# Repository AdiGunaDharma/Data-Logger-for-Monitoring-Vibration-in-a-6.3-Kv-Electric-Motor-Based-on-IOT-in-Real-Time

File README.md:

# Data-Logger-for-Monitoring-Vibration-in-a-6.3-Kv-Electric-Motor-Based-on-IOT-in-Real-Time
**Eagle Electronic Layout**
  1. Top Layout

  2. Bottom Layout

**Main**
  1. Vibration Measurement Points and Vibration Measurement Templates at Jeranjang PLTU

  2. Measurement Diagrams on Prototypes

  3. Arduino IDE Software Display and Blynk Application

  4. Sensor Data Amplifier Circuit

  5. Prototype Work System Flowchart

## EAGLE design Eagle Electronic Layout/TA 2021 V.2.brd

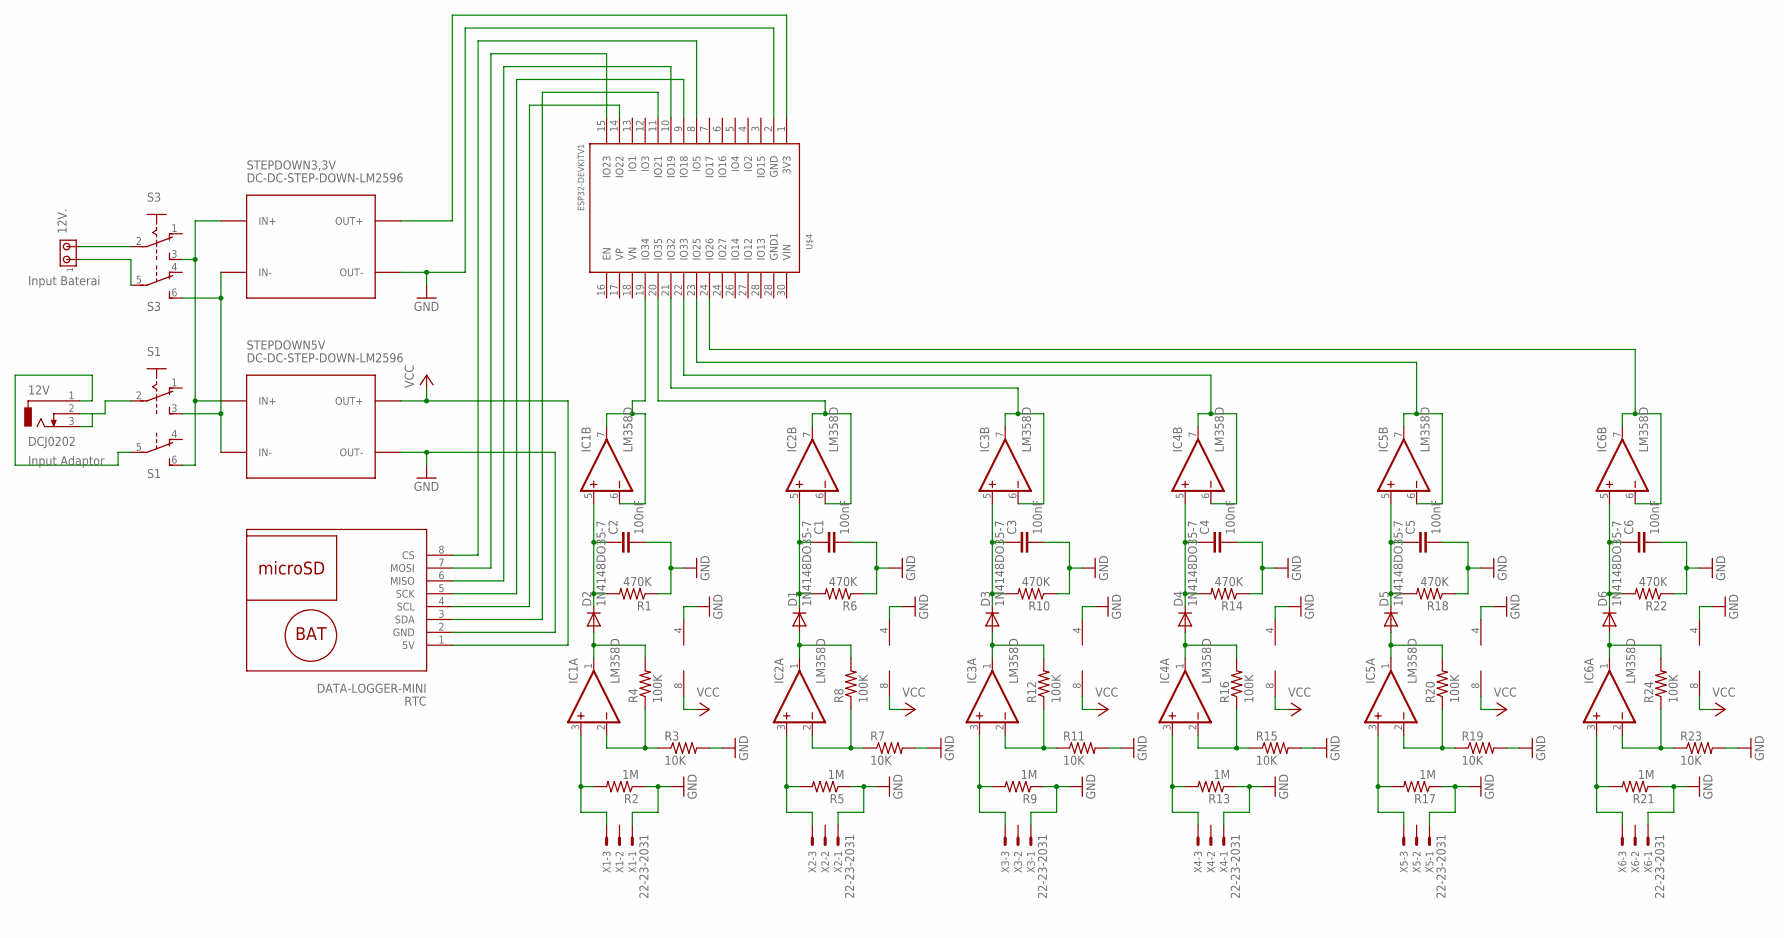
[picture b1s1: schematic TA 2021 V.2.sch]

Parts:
12V: DCJ0202
12V.: MTA02-156; 1X2MTA
C1, C2, C3, C4, C5, C6: 100nF; C075-032X103
D1, D2, D3, D4, D5, D6: 1N4148DO35-7; DO35-7
IC1, IC2, IC3, IC4, IC5, IC6: LM358D; SO08
R1, R6, R10, R14, R18, R22: 470K; 0207/10
R2, R5, R9, R13, R17, R21: 1M; 0207/10
R3, R7, R11, R15, R19, R23: 10K; 0207/10
R4, R8, R12, R16, R20, R24: 100K; 0207/10
RTC: DATA-LOGGER-MINI
S1, S3: A68-A31
STEPDOWN3,3V, STEPDOWN5V: DC-DC-STEP-DOWN-LM2596
U$4: ESP32DEVKITV1; ESP32-DEVKITV1
X1, X2, X3, X4, X5, X6: 22-23-2031

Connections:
unnamed: 12V..2, S3.2
unnamed: RTC.7 (MOSI), U$4.15 (IO23)
unnamed: S1.6 (S), S3.3 (S), STEPDOWN3,3V.IN+, STEPDOWN5V.IN+
unnamed: RTC.8 (CS), U$4.8 (IO5)
unnamed: 12V.2, 12V.3, S1.2
unnamed: RTC.6 (MISO), U$4.10 (IO19)
unnamed: 12V..1, S3.5
unnamed: RTC.5 (SCK), U$4.9 (IO18)
unnamed: 12V.1, S1.5
unnamed: C1.2, C2.2, C3.2, C4.2, C5.2, C6.2, IC1.4 (V-), IC2.4 (V-), IC3.4 (V-), IC4.4 (V-), IC5.4 (V-), IC6.4 (V-), R1.1, R2.1, R3.2, R5.1, R6.1, R7.2, R9.1, R10.1, R11.2, R13.1, R14.1, R15.2, R17.1, R18.1, R19.2, R21.1, R22.1, R23.2, RTC.2 (GND), STEPDOWN3,3V.OUT-, STEPDOWN5V.OUT-, U$4.2 (GND), X1.1, X2.1, X3.1, X4.1, X5.1, X6.1
unnamed: S1.3 (S), S3.6 (S), STEPDOWN3,3V.IN-, STEPDOWN5V.IN-
unnamed: IC2.6 (-IN), IC2.7 (OUT), U$4.20 (IO35)
unnamed: D1.A, IC2.1 (OUT), R8.2
unnamed: IC2.2 (-IN), R7.1, R8.1
unnamed: RTC.4 (SCL), U$4.14 (IO22)
unnamed: IC3.6 (-IN), IC3.7 (OUT), U$4.21 (IO32)
unnamed: STEPDOWN3,3V.OUT+, U$4.1 (3V3)
unnamed: IC4.6 (-IN), IC4.7 (OUT), U$4.22 (IO33)
unnamed: IC5.6 (-IN), IC5.7 (OUT), U$4.23 (IO25)
unnamed: IC6.6 (-IN), IC6.7 (OUT), U$4.24 (IO27)
unnamed: RTC.3 (SDA), U$4.11 (IO21)
unnamed: IC1.3 (+IN), R2.2, X1.3
unnamed: C1.1, D1.C, IC2.5 (+IN), R6.2
unnamed: D2.A, IC1.1 (OUT), R4.2
unnamed: IC1.2 (-IN), R3.1, R4.1
unnamed: C2.1, D2.C, IC1.5 (+IN), R1.2
unnamed: D4.A, IC4.1 (OUT), R16.2
unnamed: IC1.6 (-IN), IC1.7 (OUT), U$4.19 (IO34)
unnamed: IC2.3 (+IN), R5.2, X2.3
unnamed: D3.A, IC3.1 (OUT), R12.2
unnamed: C3.1, D3.C, IC3.5 (+IN), R10.2
unnamed: D6.A, IC6.1 (OUT), R24.2
unnamed: IC3.3 (+IN), R9.2, X3.3
unnamed: IC4.2 (-IN), R15.1, R16.1
unnamed: IC6.2 (-IN), R23.1, R24.1
unnamed: IC4.3 (+IN), R13.2, X4.3
unnamed: D5.A, IC5.1 (OUT), R20.2
unnamed: IC5.2 (-IN), R19.1, R20.1
unnamed: C5.1, D5.C, IC5.5 (+IN), R18.2
unnamed: IC5.3 (+IN), R17.2, X5.3
unnamed: IC6.3 (+IN), R21.2, X6.3
unnamed: IC3.2 (-IN), R11.1, R12.1
unnamed: C6.1, D6.C, IC6.5 (+IN), R22.2
unnamed: C4.1, D4.C, IC4.5 (+IN), R14.2
VCC: IC1.8 (V+), IC2.8 (V+), IC3.8 (V+), IC4.8 (V+), IC5.8 (V+), IC6.8 (V+), RTC.1 (5V), STEPDOWN5V.OUT+

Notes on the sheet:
Input Baterai
Input Adaptor

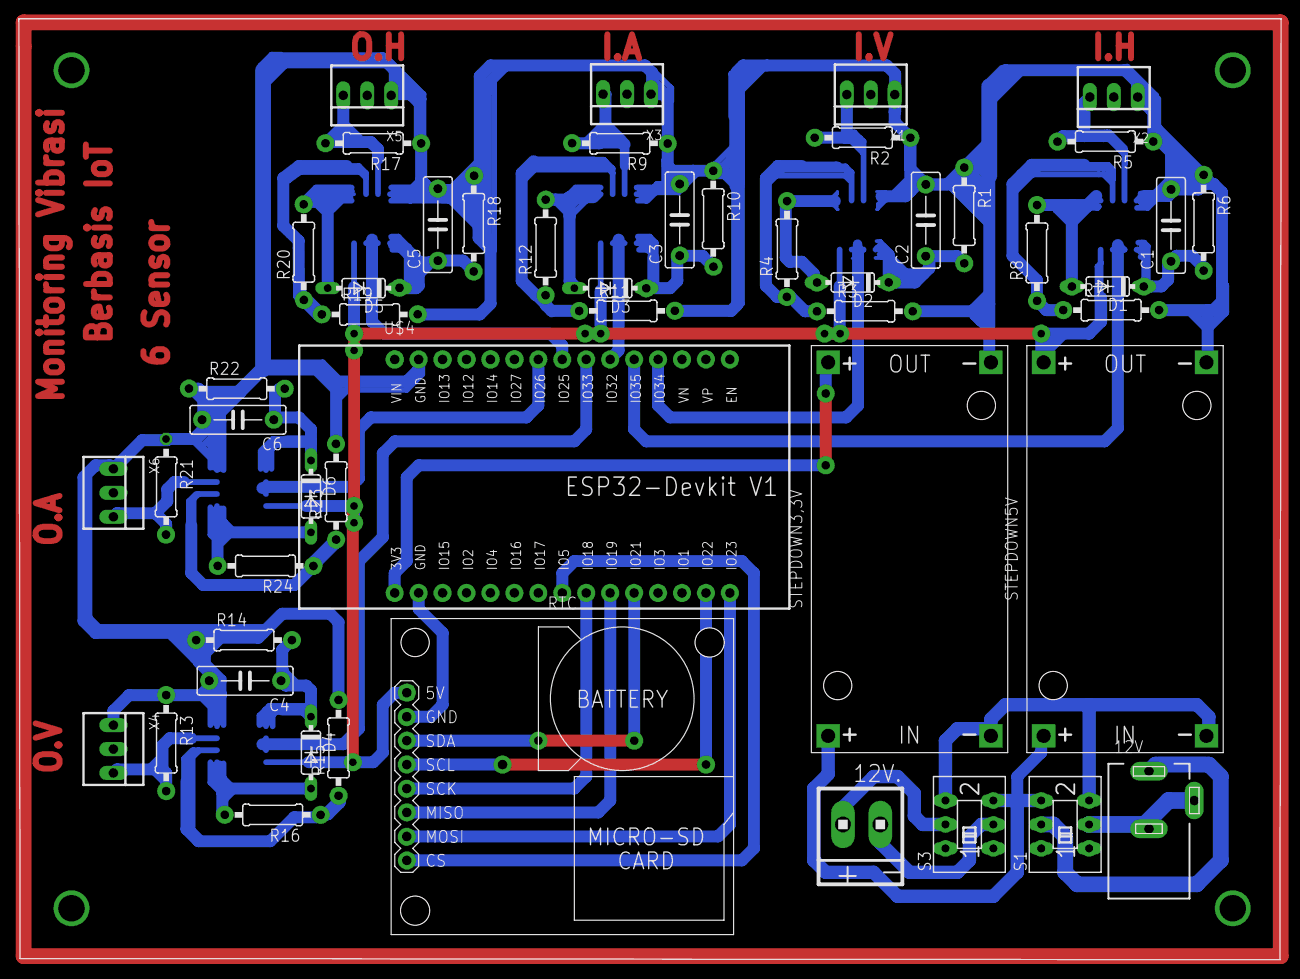
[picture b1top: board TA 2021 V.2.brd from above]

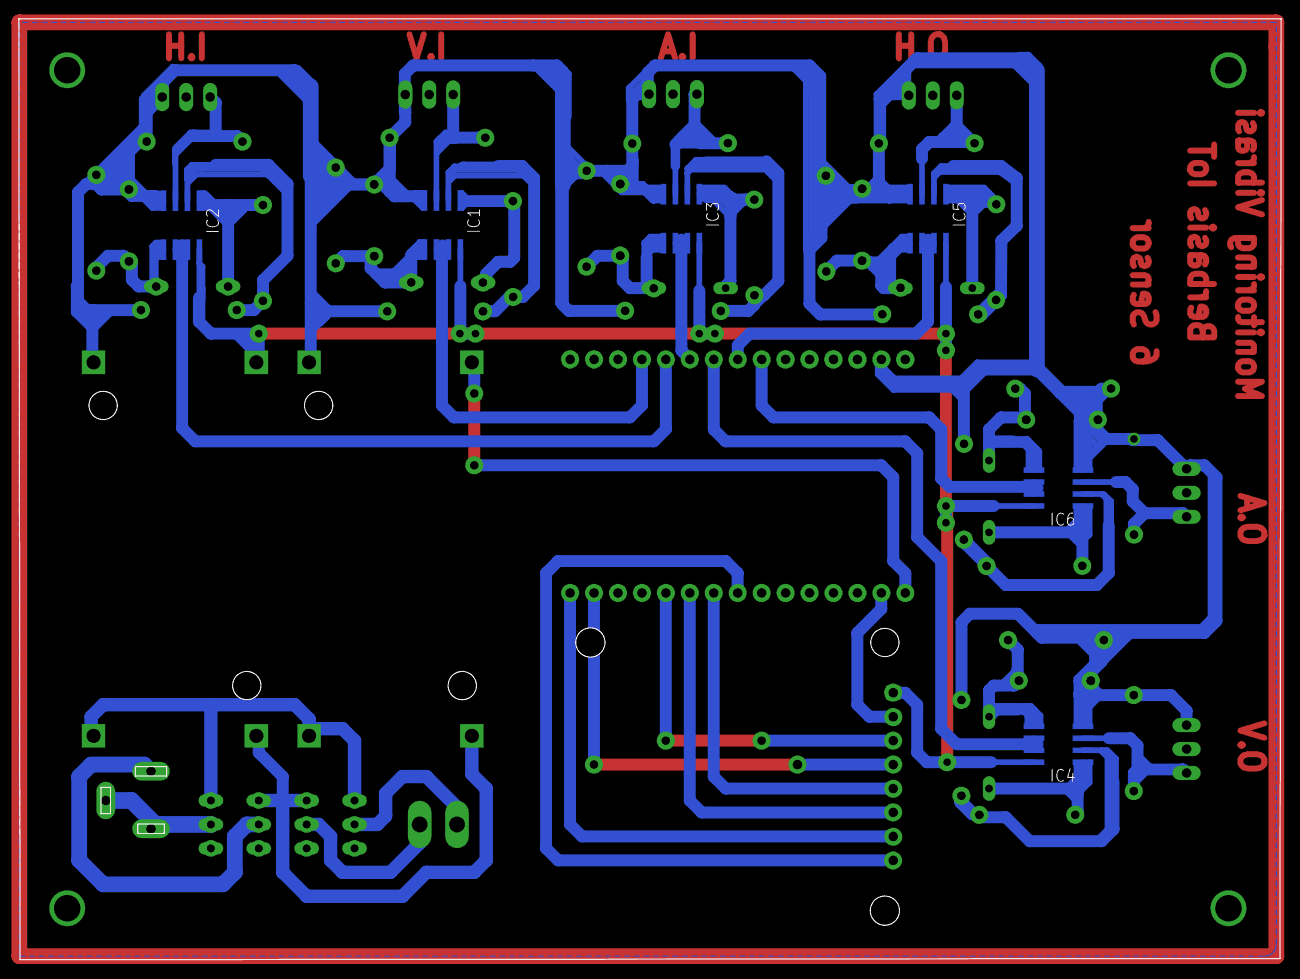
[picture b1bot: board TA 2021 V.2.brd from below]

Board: 2 copper layers, 133.9 x 99.8 mm, 56 parts (6 on the bottom side), 45 nets.

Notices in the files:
parts and their libraries:
diy-modules: Released under the Creative Commons Attribution 4.0 International License: http://creativecommons.org/licenses/by/4.0
